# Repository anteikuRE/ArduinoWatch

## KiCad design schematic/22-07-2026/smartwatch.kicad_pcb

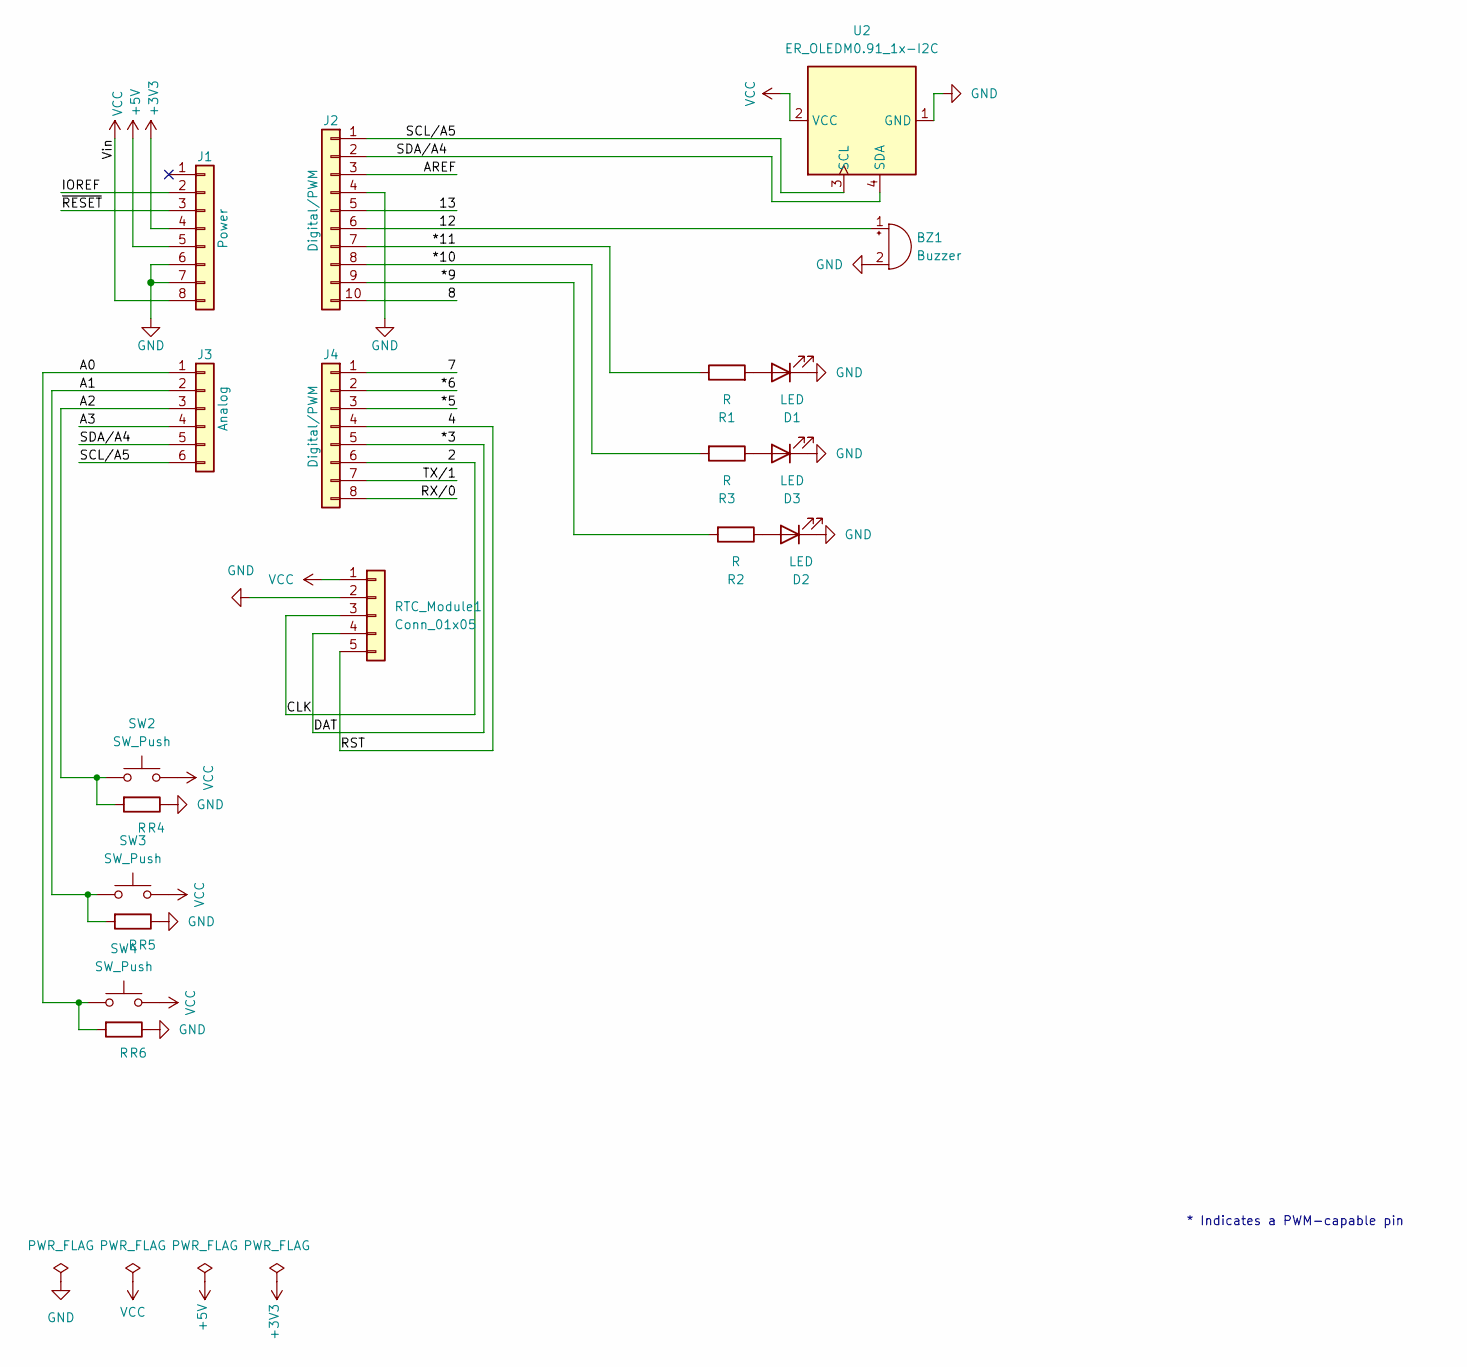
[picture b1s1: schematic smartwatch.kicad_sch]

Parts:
BZ1: Buzzer; MagneticBuzzer_CUI_CMT-8504-100-SMT
D1, D2, D3: LED; LED_D5.0mm
J1: Power; PinSocket_1x08_P2.54mm_Vertical
J2: Digital/PWM; PinSocket_1x10_P2.54mm_Vertical
J3: Analog; PinSocket_1x06_P2.54mm_Vertical
J4: Digital/PWM; PinSocket_1x08_P2.54mm_Vertical
R1, R2, R3, R4, R5, R6: R; R_Axial_DIN0207_L6.3mm_D2.5mm_P10.16mm_Horizontal
RTC_Module1: Conn_01x05; PinHeader_1x05_P2.54mm_Vertical
SW2, SW3, SW4: SW_Push; SW_PUSH_6mm
U2: ER_OLEDM0.91_1x-I2C

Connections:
+3V3: J1.4
+5V: J1.5
/2: J4.6, RTC_Module1.3
/4: J4.4, RTC_Module1.5
/7: J4.1
/8: J2.10
/12: BZ1.1 (+), J2.6
/13: J2.5
/*3: J4.5, RTC_Module1.4
/*5: J4.3
/*6: J4.2
/*9: J2.9, R2.2
/*10: J2.8, R3.2
/*11: J2.7, R1.1
/A0: J3.1, R6.2, SW4.1
/A1: J3.2, R5.2, SW3.1
/A2: J3.3, R4.2, SW2.1
/A3: J3.4
/AREF: J2.3
/IOREF: J1.2
/RX/0: J4.8
/SCL/A5: J2.1, J3.6, U2.3 (SCL)
/SDA/A4: J2.2, J3.5, U2.4 (SDA)
/TX/1: J4.7
/~RESET: J1.3
GND: BZ1.2 (-), D1.1 (K), D2.1 (K), D3.1 (K), J1.6, J1.7, J2.4, R4.1, R5.1, R6.1, RTC_Module1.2, U2.1 (GND)
unnamed: D1.2 (A), R1.2
unnamed: D2.2 (A), R2.1
unnamed: D3.2 (A), R3.1
VCC: J1.8, RTC_Module1.1, SW2.2, SW3.2, SW4.2, U2.2 (VCC)

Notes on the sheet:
* Indicates a PWM-capable pin

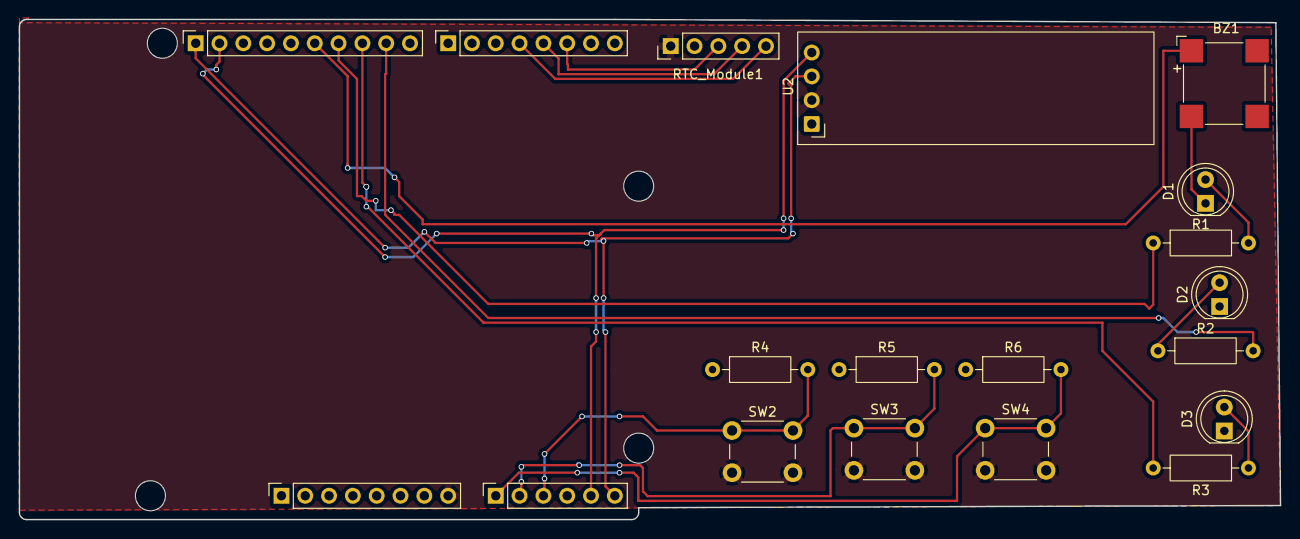
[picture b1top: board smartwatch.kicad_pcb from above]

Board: 2 copper layers, 134.5 x 53.3 mm, 23 parts (0 on the bottom side), 17 nets.

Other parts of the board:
MH1, MH2, MH3, MH4: MountingHole_3.2mm
